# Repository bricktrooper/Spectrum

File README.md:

# Spectrum

Spectrum is a 10-band stereo graphic equalizer circuit.  It uses active band pass filters in a multiple feedback configuration.  Each band can be individually amplified or attenuated using linear potentiometers.  The circuit requires an external power source of at least 5 V at 250 mA.

## Background

### Graphic Equalizers

A graphic equalizer is a piece of audio equipment that isolates different ranges of frequencies from an audio signal.  These ranges can then be individually amplified (boosted) or attenuated (cut).  The modified signals are mixed back together into a single audio signal which appears at the output.  The resulting signal is the same audio but with each frequency range adjusted with a desired gain.

### Stereo Sound

The most basic form of electrical audio signals is "mono".  This is a single audio signal that plays through all the speakers.  "Stereo" uses two separate audio signals that differ slightly but can be used to give the perception of spatial audio.  Typically, the signals are used to drive separate "left" and "right" speakers.  A graphic equalizer only operates on a single mono signal.  Spectrum effectively uses two identical mono circuits to modify both channels of stereo audio.  The resulting output can be played through stereo headphones.  The circuit must be powered by an external wall adapter or any other 5 V source that can supply approximately 250 mA of current.

## Circuit Design

### Power Supply

Spectrum uses a 5 V power supply that is regulated by an L7805 LDO.  Traditionally, operational amplifiers use a bipolar supply of +VDD and -VDD, with the ground point of the signal being 0 V.  This is not possible with a single supply.  Therefore, Spectrum raises the ground point to a virtual ground of (VDD / 2), or 2.5 V.  The op amps are supplied by 5 V and sink to 0 V (GND).  This provides 2.5 V of signal swing, which is enough for driving headphones to a considerable volume.  To drive large speakers, a separate amplifier should be used.  Capacitive coupling is used to inject an AC audio signal into a 2.5 V bias and decouple the bias at the output headphone jack.

### Preamplifier

The preamplifier's job is to drive the rest of the circuit, effectively isolating the input resistance of the circuit from the audio source.  This is important because headphone jack outputs cannot drive very high impedances.  The preamplifer is also capable of amplifying or attenuating the input signal.  Amplification may be required if the input source is too quiet, while attenuation can be used to reduce distortion in the output signal.  The input to the preamplifier is further isolated using a 1:1 audio transformer.  This prevents the ground of the circuit from creating a ground loop through the audio cable, which creates an undesirable humming noise due to the oscillation of the AC mains voltage.  The preamplifier is implemented as a simple inverting amplifier.  A capacitor is used at the input to strip out any existing DC voltage and the output signal is re-biased at the virtual ground point.  A potentiometer is used in the feedback resistance to amplify or attenuate the signal linearly.

### Band Pass Filters

The core circuit of a graphic equalizer is the band pass filter, which isolates a range of frequencies.  Different resistor and capacitor values are used to achieve different cutoff frequencies over the bass, mid, and treble ranges.  Spectrum uses 10 filters for each audio channel.  The centre frequencies are chosen based on standard octaves:

- 31.5 Hz
- 63 Hz
- 125 Hz
- 250 Hz
- 500 Hz
- 1 kHz
- 2 kHz
- 4 kHz
- 8 kHz
- 16 kHz

These are active filters that used op amps in the multiple-feedback configuration, which allows the cutoff frequency to be changed without affecting the gain of the centre frequency.  The gain of all the filters have been adjusted so that the entire audio range has a flat gain response when the filter outputs are mixed back together.  Each individual filter has a DC gain of 1 V/V, with the exception of 31.5 Hz and 16 kHz, which have a gain of 1.6 V/V.  A quality factor of Q = 1.7 is used for all filters.  The component selection is as follows:

```
-------------------------------------------------------------------------------------------------------------------
| BAND    | ERROR      | C          | R1         | R2         | R3         | f          | Q          | A          |
-------------------------------------------------------------------------------------------------------------------
| 31.5 Hz | 0.816      | 0.33 uF    | 16 K       | 51 K       | 6.2 K      | 31.948 Hz  | 1.689      | 1.594 V/V  |
| 63 Hz   | 0.745      | 0.56 uF    | 7.5 K      | 15 K       | 1.6 K      | 63.902 Hz  | 1.686      | 1.000 V/V  |
| 125 Hz  | 0.709      | 0.22 uF    | 10 K       | 20 K       | 2 K        | 125.302 Hz | 1.732      | 1.000 V/V  |
| 250 Hz  | 0.709      | 0.1 uF     | 11 K       | 22 K       | 2.2 K      | 250.604 Hz | 1.732      | 1.000 V/V  |
| 500 Hz  | 1.204      | 0.1 uF     | 5.6 K      | 11 K       | 1.1 K      | 500.462 Hz | 1.729      | 0.982 V/V  |
| 1 kHz   | 1.328      | 0.18 uF    | 1.5 K      | 3 K        | 0.3 K      | 1.021 kHz  | 1.732      | 1.000 V/V  |
| 2 kHz   | 0.467      | 0.18 uF    | 0.75 K     | 1.5 K      | 0.16 K     | 1.988 kHz  | 1.686      | 1.000 V/V  |
| 4 kHz   | 1.078      | 0.068 uF   | 1 K        | 2 K        | 0.2 K      | 4.054 kHz  | 1.732      | 1.000 V/V  |
| 8 kHz   | 0.812      | 0.033 uF   | 1 K        | 2 K        | 0.22 K     | 8.031 kHz  | 1.665      | 1.000 V/V  |
| 16 kHz  | 0.916      | 0.022 uF   | 0.47 K     | 1.5 K      | 0.18 K     | 16.373 kHz | 1.697      | 1.596 V/V  |
-------------------------------------------------------------------------------------------------------------------
```

### Band Amplifiers

Each band pass filter is followed by an inverting amplifier, which has adjustable gain via a potentiometer in the feedback path.  This allows the user to individually boost or cut different frequency ranges.  At the potentiometer neutral point, the gain of the band amplifier is 0.5 V/V, meaning that each band can be attenuated down to 0 V/V or boosted up to 1 V/V, which is the gain of the band pass filters.  Any further amplification must be provided from the audio source and the preamplifier.  Due to band overlap, the actual realized gain is slightly higher or lower than in theory.  This is a tradeoff between selectivity and gain accuracy.

### Mixer

The mixer is a summing amplifier that re-combines all the band signals back into a single audio signal.  It has a fixed gain of 5 V/V, and the output signal can directly drive low-impedance headphones.  The output signal runs through a large capacitor to cut out the virtual ground DC bias to avoid damaging the headphone speaker coils.  This turns the signal into an AC waveform with a GND as the reference point.

## Schematic

## Circuit Board

### Top

### Bottom

### Assembled

## Revisions

- A 470R resistor was added to the audio output to mitigate the amplified hissing noise.  The side effect of this is reduced gain from the preamp and increased distortion in the output signal.

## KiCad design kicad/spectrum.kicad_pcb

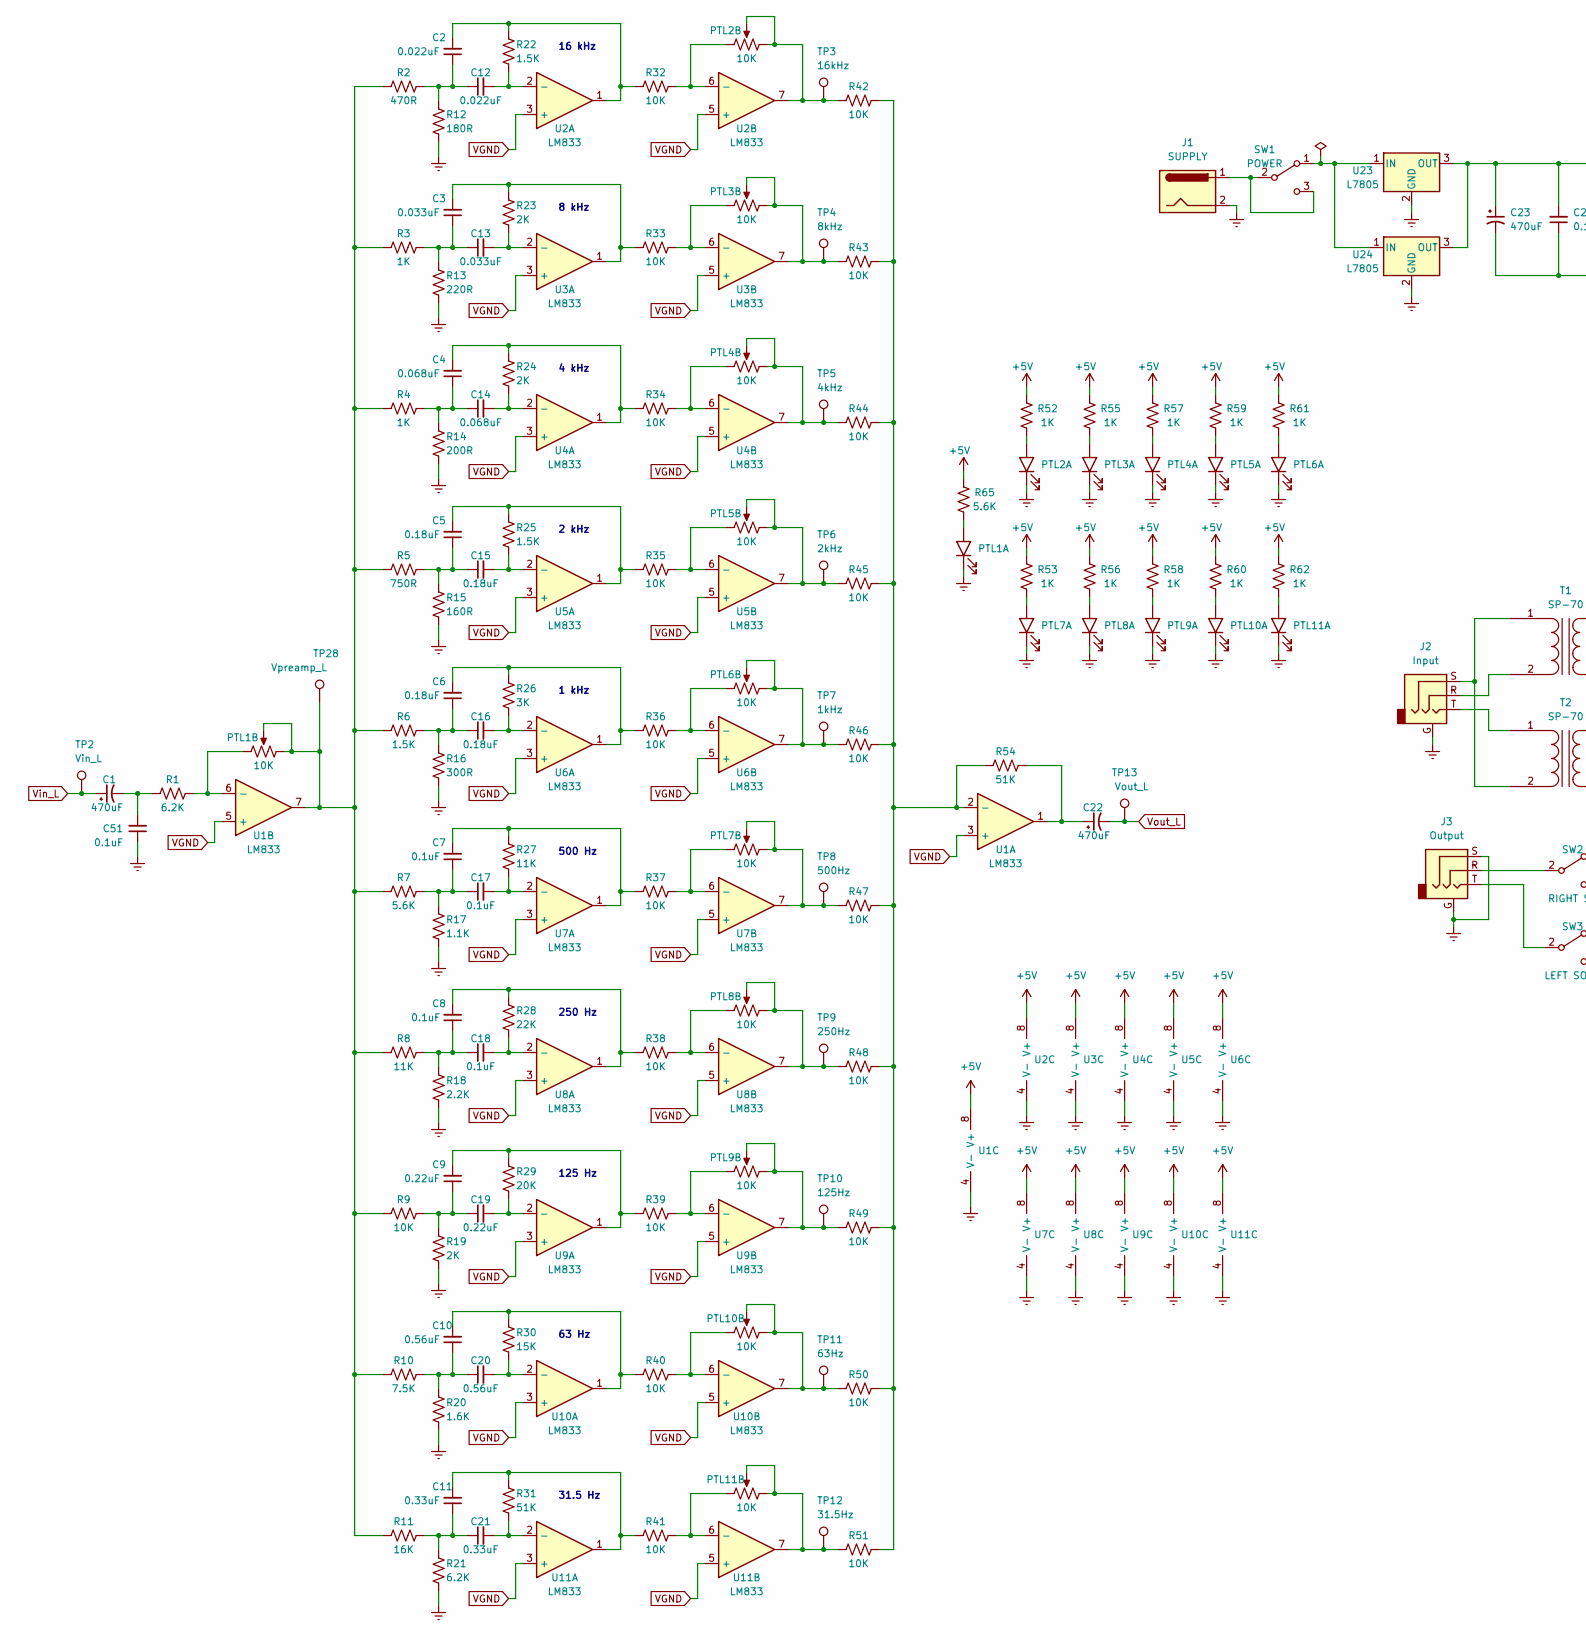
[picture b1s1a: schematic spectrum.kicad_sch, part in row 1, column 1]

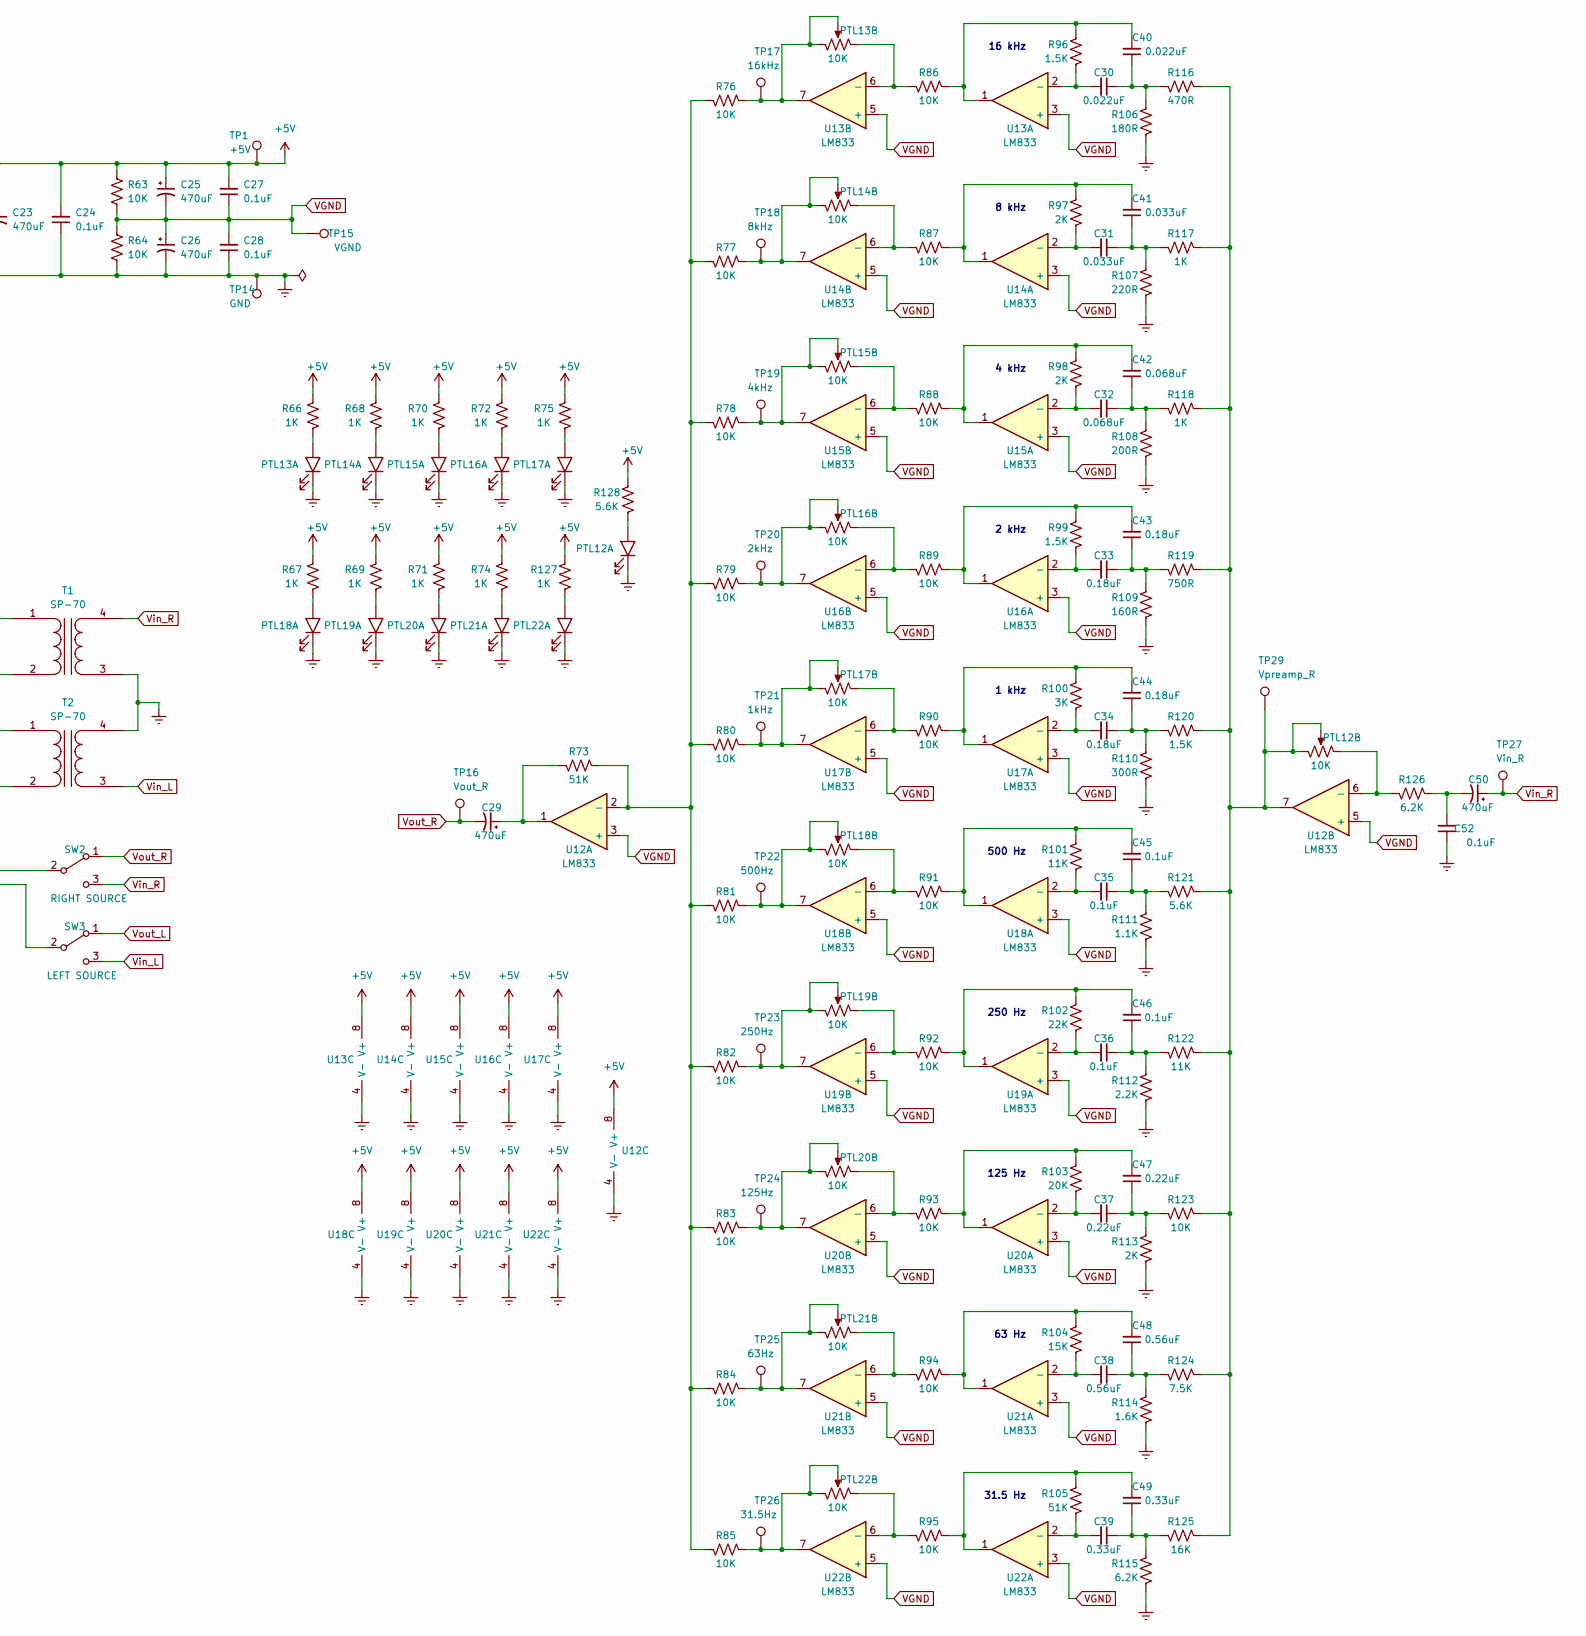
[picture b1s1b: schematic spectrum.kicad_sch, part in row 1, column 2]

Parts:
C1, C22, C23, C25, C26, C29, C50: 470uF; CP_Radial_D8.0mm_P3.50mm
C2, C12, C30, C40: 0.022uF; C_Disc_D4.3mm_W1.9mm_P5.00mm
C3, C13, C31, C41: 0.033uF; C_Disc_D4.3mm_W1.9mm_P5.00mm
C4, C14, C32, C42: 0.068uF; C_Disc_D4.3mm_W1.9mm_P5.00mm
C5, C6, C15, C16, C33, C34, C43, C44: 0.18uF; C_Disc_D4.3mm_W1.9mm_P5.00mm
C7, C8, C17, C18, C24, C27, C28, C35, C36, C45, C46, C51, C52: 0.1uF; C_Disc_D4.3mm_W1.9mm_P5.00mm
C9, C19, C37, C47: 0.22uF; C_Disc_D4.3mm_W1.9mm_P5.00mm
C10, C20, C38, C48: 0.56uF; C_Disc_D4.3mm_W1.9mm_P5.00mm
C11, C21, C39, C49: 0.33uF; C_Disc_D4.3mm_W1.9mm_P5.00mm
J1: SUPPLY; BarrelJack_Horizontal
J2: Input; STX35013N
J3: Output; STX35013N
PTL1, PTL2, PTL3, PTL4, PTL5, PTL6, PTL7, PTL8, PTL9, PTL10, PTL11, PTL12, PTL13, PTL14, PTL15, PTL16, PTL17, PTL18, PTL19, PTL20, PTL21, PTL22: 10K; PTL30
R1, R21, R115, R126: 6.2K; R_Axial_DIN0207_L6.3mm_D2.5mm_P7.62mm_Horizontal
R2, R116: 470R; R_Axial_DIN0207_L6.3mm_D2.5mm_P7.62mm_Horizontal
R3, R4, R52, R53, R55, R56, R57, R58, R59, R60, R61, R62, R66, R67, R68, R69, R70, R71, R72, R74, R75, R117, R118, R127: 1K; R_Axial_DIN0207_L6.3mm_D2.5mm_P7.62mm_Horizontal
R5, R119: 750R; R_Axial_DIN0207_L6.3mm_D2.5mm_P7.62mm_Horizontal
R6, R22, R25, R96, R99, R120: 1.5K; R_Axial_DIN0207_L6.3mm_D2.5mm_P7.62mm_Horizontal
R7, R65, R121, R128: 5.6K; R_Axial_DIN0207_L6.3mm_D2.5mm_P7.62mm_Horizontal
R8, R27, R101, R122: 11K; R_Axial_DIN0207_L6.3mm_D2.5mm_P7.62mm_Horizontal
R9, R32, R33, R34, R35, R36, R37, R38, R39, R40, R41, R42, R43, R44, R45, R46, R47, R48, R49, R50, R51, R63, R64, R76, R77, R78, R79, R80, R81, R82, R83, R84, R85, R86, R87, R88, R89, R90, R91, R92, R93, R94, R95, R123: 10K; R_Axial_DIN0207_L6.3mm_D2.5mm_P7.62mm_Horizontal
R10, R124: 7.5K; R_Axial_DIN0207_L6.3mm_D2.5mm_P7.62mm_Horizontal
R11, R125: 16K; R_Axial_DIN0207_L6.3mm_D2.5mm_P7.62mm_Horizontal
R12, R106: 180R; R_Axial_DIN0207_L6.3mm_D2.5mm_P7.62mm_Horizontal
R13, R107: 220R; R_Axial_DIN0207_L6.3mm_D2.5mm_P7.62mm_Horizontal
R14, R108: 200R; R_Axial_DIN0207_L6.3mm_D2.5mm_P7.62mm_Horizontal
R15, R109: 160R; R_Axial_DIN0207_L6.3mm_D2.5mm_P7.62mm_Horizontal
R16, R110: 300R; R_Axial_DIN0207_L6.3mm_D2.5mm_P7.62mm_Horizontal
R17, R111: 1.1K; R_Axial_DIN0207_L6.3mm_D2.5mm_P7.62mm_Horizontal
R18, R112: 2.2K; R_Axial_DIN0207_L6.3mm_D2.5mm_P7.62mm_Horizontal
R19, R23, R24, R97, R98, R113: 2K; R_Axial_DIN0207_L6.3mm_D2.5mm_P7.62mm_Horizontal
R20, R114: 1.6K; R_Axial_DIN0207_L6.3mm_D2.5mm_P7.62mm_Horizontal
R26, R100: 3K; R_Axial_DIN0207_L6.3mm_D2.5mm_P7.62mm_Horizontal
R28, R102: 22K; R_Axial_DIN0207_L6.3mm_D2.5mm_P7.62mm_Horizontal
R29, R103: 20K; R_Axial_DIN0207_L6.3mm_D2.5mm_P7.62mm_Horizontal
R30, R104: 15K; R_Axial_DIN0207_L6.3mm_D2.5mm_P7.62mm_Horizontal
R31, R54, R73, R105: 51K; R_Axial_DIN0207_L6.3mm_D2.5mm_P7.62mm_Horizontal
SW1: POWER; SW_1101M2S3CQE2
SW2: RIGHT SOURCE; SW_1101M2S3CQE2
SW3: LEFT SOURCE; SW_1101M2S3CQE2
T1, T2: SP-70; SP70
TP1: +5V; TestPoint_Keystone_5000-5004_Miniature
TP2: Vin_L; TestPoint_Keystone_5000-5004_Miniature
TP3, TP17: 16kHz; TestPoint_Keystone_5000-5004_Miniature
TP4, TP18: 8kHz; TestPoint_Keystone_5000-5004_Miniature
TP5, TP19: 4kHz; TestPoint_Keystone_5000-5004_Miniature
TP6, TP20: 2kHz; TestPoint_Keystone_5000-5004_Miniature
TP7, TP21: 1kHz; TestPoint_Keystone_5000-5004_Miniature
TP8, TP22: 500Hz; TestPoint_Keystone_5000-5004_Miniature
TP9, TP23: 250Hz; TestPoint_Keystone_5000-5004_Miniature
TP10, TP24: 125Hz; TestPoint_Keystone_5000-5004_Miniature
TP11, TP25: 63Hz; TestPoint_Keystone_5000-5004_Miniature
TP12, TP26: 31.5Hz; TestPoint_Keystone_5000-5004_Miniature
TP13: Vout_L; TestPoint_Keystone_5000-5004_Miniature
TP14: GND; TestPoint_Keystone_5000-5004_Miniature
TP15: VGND; TestPoint_Keystone_5000-5004_Miniature
TP16: Vout_R; TestPoint_Keystone_5000-5004_Miniature
TP27: Vin_R; TestPoint_Keystone_5000-5004_Miniature
TP28: Vpreamp_L; TestPoint_Keystone_5000-5004_Miniature
TP29: Vpreamp_R; TestPoint_Keystone_5000-5004_Miniature
U1, U2, U3, U4, U5, U6, U7, U8, U9, U10, U11, U12, U13, U14, U15, U16, U17, U18, U19, U20, U21, U22: LM833; DIP-8_W7.62mm_Socket_LongPads
U23, U24: L7805; TO-220-3_Vertical

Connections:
+5V: C23.1, C24.2, C25.1, C27.2, R52.1, R53.1, R55.1, R56.1, R57.1, R58.1, R59.1, R60.1, R61.1, R62.1, R63.1, R65.1, R66.1, R67.1, R68.1, R69.1, R70.1, R71.1, R72.1, R74.1, R75.1, R127.1, R128.1, TP1.1, U1.8 (V+), U2.8 (V+), U3.8 (V+), U4.8 (V+), U5.8 (V+), U6.8 (V+), U7.8 (V+), U8.8 (V+), U9.8 (V+), U10.8 (V+), U11.8 (V+), U12.8 (V+), U13.8 (V+), U14.8 (V+), U15.8 (V+), U16.8 (V+), U17.8 (V+), U18.8 (V+), U19.8 (V+), U20.8 (V+), U21.8 (V+), U22.8 (V+), U23.3 (OUT), U24.3 (OUT)
GNDREF: C23.2, C24.1, C26.2, C28.1, C51.1, C52.1, J1.2, J2.G, J3.G, J3.S, PTL1.5 (E), PTL2.5 (E), PTL3.5 (E), PTL4.5 (E), PTL5.5 (E), PTL6.5 (E), PTL7.5 (E), PTL8.5 (E), PTL9.5 (E), PTL10.5 (E), PTL11.5 (E), PTL12.5 (E), PTL13.5 (E), PTL14.5 (E), PTL15.5 (E), PTL16.5 (E), PTL17.5 (E), PTL18.5 (E), PTL19.5 (E), PTL20.5 (E), PTL21.5 (E), PTL22.5 (E), R12.2, R13.2, R14.2, R15.2, R16.2, R17.2, R18.2, R19.2, R20.2, R21.2, R64.2, R106.2, R107.2, R108.2, R109.2, R110.2, R111.2, R112.2, R113.2, R114.2, R115.2, T1.3 (SA), T2.4 (SB), TP14.1, U1.4 (V-), U2.4 (V-), U3.4 (V-), U4.4 (V-), U5.4 (V-), U6.4 (V-), U7.4 (V-), U8.4 (V-), U9.4 (V-), U10.4 (V-), U11.4 (V-), U12.4 (V-), U13.4 (V-), U14.4 (V-), U15.4 (V-), U16.4 (V-), U17.4 (V-), U18.4 (V-), U19.4 (V-), U20.4 (V-), U21.4 (V-), U22.4 (V-), U23.2 (GND), U24.2 (GND)
unnamed: C1.2, C51.2, R1.2
unnamed: C2.2, R22.1, R32.2, U2.1
unnamed: C3.2, R23.1, R33.2, U3.1
unnamed: C4.2, R24.1, R34.2, U4.1
unnamed: C5.2, R25.1, R35.2, U5.1
unnamed: C6.2, R26.1, R36.2, U6.1
unnamed: C7.2, R27.1, R37.2, U7.1
unnamed: C8.2, R28.1, R38.2, U8.1
unnamed: C9.2, R29.1, R39.2, U9.1
unnamed: C10.1, C20.1, R10.1, R20.1
unnamed: C10.2, R30.1, R40.2, U10.1
unnamed: C11.1, C21.1, R11.1, R21.1
unnamed: C11.2, R31.1, R41.2, U11.1
unnamed: C2.1, C12.1, R2.1, R12.1
unnamed: C12.2, R22.2, U2.2 (-)
unnamed: C3.1, C13.1, R3.1, R13.1
unnamed: C13.2, R23.2, U3.2 (-)
unnamed: C4.1, C14.1, R4.1, R14.1
unnamed: C14.2, R24.2, U4.2 (-)
unnamed: C5.1, C15.1, R5.1, R15.1
unnamed: C15.2, R25.2, U5.2 (-)
unnamed: C6.1, C16.1, R6.1, R16.1
unnamed: C16.2, R26.2, U6.2 (-)
unnamed: C7.1, C17.1, R7.1, R17.1
unnamed: C17.2, R27.2, U7.2 (-)
unnamed: C8.1, C18.1, R8.1, R18.1
unnamed: C18.2, R28.2, U8.2 (-)
unnamed: C9.1, C19.1, R9.1, R19.1
unnamed: C19.2, R29.2, U9.2 (-)
unnamed: C20.2, R30.2, U10.2 (-)
unnamed: C21.2, R31.2, U11.2 (-)
unnamed: C22.1, R54.1, U1.1
unnamed: C29.1, R73.1, U12.1
unnamed: C30.1, C40.1, R106.1, R116.1
unnamed: C30.2, R96.2, U13.2 (-)
unnamed: C31.1, C41.1, R107.1, R117.1
unnamed: C31.2, R97.2, U14.2 (-)
unnamed: C32.1, C42.1, R108.1, R118.1
unnamed: C32.2, R98.2, U15.2 (-)
unnamed: C33.1, C43.1, R109.1, R119.1
unnamed: C33.2, R99.2, U16.2 (-)
unnamed: C34.1, C44.1, R110.1, R120.1
unnamed: C34.2, R100.2, U17.2 (-)
unnamed: C35.1, C45.1, R111.1, R121.1
unnamed: C35.2, R101.2, U18.2 (-)
unnamed: C36.1, C46.1, R112.1, R122.1
unnamed: C36.2, R102.2, U19.2 (-)
unnamed: C37.1, C47.1, R113.1, R123.1
unnamed: C37.2, R103.2, U20.2 (-)
unnamed: C38.1, C48.1, R114.1, R124.1
unnamed: C38.2, R104.2, U21.2 (-)
unnamed: C39.1, C49.1, R115.1, R125.1
unnamed: C39.2, R105.2, U22.2 (-)
unnamed: C40.2, R86.2, R96.1, U13.1
unnamed: C41.2, R87.2, R97.1, U14.1
unnamed: C42.2, R88.2, R98.1, U15.1
unnamed: C43.2, R89.2, R99.1, U16.1
unnamed: C44.2, R90.2, R100.1, U17.1
unnamed: C45.2, R91.2, R101.1, U18.1
unnamed: C46.2, R92.2, R102.1, U19.1
unnamed: C47.2, R93.2, R103.1, U20.1
unnamed: C48.2, R94.2, R104.1, U21.1
unnamed: C49.2, R95.2, R105.1, U22.1
unnamed: C50.2, C52.2, R126.2
unnamed: J1.1, SW1.2 (B), SW1.3 (C)
unnamed: J2.R, T1.2 (AB)
unnamed: J2.S, T1.1 (AA), T2.2 (AB)
unnamed: J2.T, T2.1 (AA)
unnamed: J3.R, SW2.2 (B)
unnamed: J3.T, SW3.2 (B)
unnamed: PTL1.1, R1.1, U1.6 (-)
unnamed: PTL1.2, PTL1.3, R2.2, R3.2, R4.2, R5.2, R6.2, R7.2, R8.2, R9.2, R10.2, R11.2, TP28.1, U1.7
unnamed: PTL1.4 (B), R65.2
unnamed: PTL2.1, R32.1, U2.6 (-)
unnamed: PTL2.2, PTL2.3, R42.2, TP3.1, U2.7
unnamed: PTL2.4 (B), R52.2
unnamed: PTL3.1, R33.1, U3.6 (-)
unnamed: PTL3.2, PTL3.3, R43.2, TP4.1, U3.7
unnamed: PTL3.4 (B), R55.2
unnamed: PTL4.1, R34.1, U4.6 (-)
unnamed: PTL4.2, PTL4.3, R44.2, TP5.1, U4.7
unnamed: PTL4.4 (B), R57.2
unnamed: PTL5.1, R35.1, U5.6 (-)
unnamed: PTL5.2, PTL5.3, R45.2, TP6.1, U5.7
unnamed: PTL5.4 (B), R59.2
unnamed: PTL6.1, R36.1, U6.6 (-)
unnamed: PTL6.2, PTL6.3, R46.2, TP7.1, U6.7
unnamed: PTL6.4 (B), R61.2
unnamed: PTL7.1, R37.1, U7.6 (-)
unnamed: PTL7.2, PTL7.3, R47.2, TP8.1, U7.7
unnamed: PTL7.4 (B), R53.2
unnamed: PTL8.1, R38.1, U8.6 (-)
unnamed: PTL8.2, PTL8.3, R48.2, TP9.1, U8.7
unnamed: PTL8.4 (B), R56.2
unnamed: PTL9.1, R39.1, U9.6 (-)
unnamed: PTL9.2, PTL9.3, R49.2, TP10.1, U9.7
unnamed: PTL9.4 (B), R58.2
unnamed: PTL10.1, R40.1, U10.6 (-)
unnamed: PTL10.2, PTL10.3, R50.2, TP11.1, U10.7
unnamed: PTL10.4 (B), R60.2
unnamed: PTL11.1, R41.1, U11.6 (-)
unnamed: PTL11.2, PTL11.3, R51.2, TP12.1, U11.7
unnamed: PTL11.4 (B), R62.2
unnamed: PTL12.1, R126.1, U12.6 (-)
unnamed: PTL12.2, PTL12.3, R116.2, R117.2, R118.2, R119.2, R120.2, R121.2, R122.2, R123.2, R124.2, R125.2, TP29.1, U12.7
unnamed: PTL12.4 (B), R128.2
unnamed: PTL13.1, R86.1, U13.6 (-)
unnamed: PTL13.2, PTL13.3, R76.2, TP17.1, U13.7
unnamed: PTL13.4 (B), R66.2
unnamed: PTL14.1, R87.1, U14.6 (-)
unnamed: PTL14.2, PTL14.3, R77.2, TP18.1, U14.7
unnamed: PTL14.4 (B), R68.2
unnamed: PTL15.1, R88.1, U15.6 (-)
unnamed: PTL15.2, PTL15.3, R78.2, TP19.1, U15.7
unnamed: PTL15.4 (B), R70.2
unnamed: PTL16.1, R89.1, U16.6 (-)
unnamed: PTL16.2, PTL16.3, R79.2, TP20.1, U16.7
unnamed: PTL16.4 (B), R72.2
unnamed: PTL17.1, R90.1, U17.6 (-)
unnamed: PTL17.2, PTL17.3, R80.2, TP21.1, U17.7
unnamed: PTL17.4 (B), R75.2
unnamed: PTL18.1, R91.1, U18.6 (-)
unnamed: PTL18.2, PTL18.3, R81.2, TP22.1, U18.7
unnamed: PTL18.4 (B), R67.2
unnamed: PTL19.1, R92.1, U19.6 (-)
unnamed: PTL19.2, PTL19.3, R82.2, TP23.1, U19.7
unnamed: PTL19.4 (B), R69.2
unnamed: PTL20.1, R93.1, U20.6 (-)
unnamed: PTL20.2, PTL20.3, R83.2, TP24.1, U20.7
unnamed: PTL20.4 (B), R71.2
unnamed: PTL21.1, R94.1, U21.6 (-)
unnamed: PTL21.2, PTL21.3, R84.2, TP25.1, U21.7
unnamed: PTL21.4 (B), R74.2
unnamed: PTL22.1, R95.1, U22.6 (-)
unnamed: PTL22.2, PTL22.3, R85.2, TP26.1, U22.7
unnamed: PTL22.4 (B), R127.2
unnamed: R42.1, R43.1, R44.1, R45.1, R46.1, R47.1, R48.1, R49.1, R50.1, R51.1, R54.2, U1.2 (-)
unnamed: R73.2, R76.1, R77.1, R78.1, R79.1, R80.1, R81.1, R82.1, R83.1, R84.1, R85.1, U12.2 (-)
unnamed: SW1.1 (A), U23.1 (IN), U24.1 (IN)
VGND: C25.2, C26.1, C27.1, C28.2, R63.2, R64.1, TP15.1, U1.3 (+), U1.5 (+), U2.3 (+), U2.5 (+), U3.3 (+), U3.5 (+), U4.3 (+), U4.5 (+), U5.3 (+), U5.5 (+), U6.3 (+), U6.5 (+), U7.3 (+), U7.5 (+), U8.3 (+), U8.5 (+), U9.3 (+), U9.5 (+), U10.3 (+), U10.5 (+), U11.3 (+), U11.5 (+), U12.3 (+), U12.5 (+), U13.3 (+), U13.5 (+), U14.3 (+), U14.5 (+), U15.3 (+), U15.5 (+), U16.3 (+), U16.5 (+), U17.3 (+), U17.5 (+), U18.3 (+), U18.5 (+), U19.3 (+), U19.5 (+), U20.3 (+), U20.5 (+), U21.3 (+), U21.5 (+), U22.3 (+), U22.5 (+)
Vin_L: C1.1, SW3.3 (C), T2.3 (SA), TP2.1
Vin_R: C50.1, SW2.3 (C), T1.4 (SB), TP27.1
Vout_L: C22.2, SW3.1 (A), TP13.1
Vout_R: C29.2, SW2.1 (A), TP16.1

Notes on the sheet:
16 kHz
125 Hz
250 Hz
500 Hz
4 kHz
8 kHz
63 Hz
31.5 Hz
1 kHz
2 kHz

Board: 2 copper layers, 263 parts (0 on the bottom side), 146 nets, no tracks yet.

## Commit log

2022-01-15 Add .gitignore
2022-01-17 Script for calculating optimal resistor and capacitor values
2022-01-17 Print out actual Q, f, and A
2022-01-23 Clean up R and C calculator script
2022-01-23 Relocate script
2022-01-23 Create BPF in KiCad
2022-01-23 Choose resistors and capacitors for band pass filters
2022-01-23 Modify script to match standard resistor and capacitor charts
2022-01-24 Notes
2022-01-24 Resources
2022-01-24 Cutoff frequency calculator script
2022-01-24 Pre-amplifier
2022-01-29 Fix swapped BPF input terminals to be inverting
2022-01-29 Move volume POT to preamp
2022-01-30 Notes on faders
2022-01-30 Band pass filter array
2022-01-30 Left and right stereo filters
2022-01-30 Footprint and symbol for Bourns PTL POT with LEDs
2022-01-30 Organize resources and datasheets
2022-01-30 30 mm Bourns PTL footprint
2022-01-30 Test points
2022-01-31 Switch to USB-A
2022-02-01 Resistor datasheet
2022-02-12 Increase preamp input resistor to 1K
2022-02-13 Fix POT LEDs and use barrel jack for power
2022-02-13 Footprints
2022-02-13 Organize parts
2022-02-13 Fix POT footprint and pins
2022-02-13 Filter array component layout
2022-02-13 Fix bypass routes
2022-02-14 More component layout
2022-02-28 Isolation transformer and resistor tweaks
    - Audio isolation transformer to fix ground loop hum.
    - Changed preamp Ri and mixer Rf to work compensate
    for transfomer effects.
2022-03-11 Finish component layout and add extra 7805
    - Extra 7805 needed for heat dissipation
2022-03-14 Route PCB
2022-03-14 Rounded board edges
2022-03-15 Clean up board traces and use single L7805
2022-03-16 Finalize PCB
2022-03-16 Generate Gerbers
2022-03-16 Basic README information
2022-03-22 Add GLB circuit paper from TI
2022-03-22 Remove stream-of-consciousness notes
2022-03-22 Add more documentation to README
2022-03-23 Add information and pictures to README
2022-03-23 Add schematic PDF
2022-03-28 Fix trace that was close to pad
2022-03-28 Thermal reliefs for bottom copper
    For easier hand soldering (I learned this the hard way).
2022-03-28 Spectrum II (Rev 1)
2022-04-17 Add output resistor to cut out noise
2022-04-17 Add picture of final assembled board
2022-04-26 Note revision side effects
2022-08-14 Print bandwidth in script
2022-08-14 Fix typos in README
2023-04-14 Fix README
2023-04-14 Design notes
